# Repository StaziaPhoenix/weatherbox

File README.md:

# Weatherbox
This repository contains code and schematics of the WeatherBox lamp we created for ECE 196 at UC San Diego.
## Contents
* The root directory contains the Arduino code
* The Electrical directory contains Eagle circuit schematics
* The Structural directory contains drawings and Inkscape and SolidWorks schematics

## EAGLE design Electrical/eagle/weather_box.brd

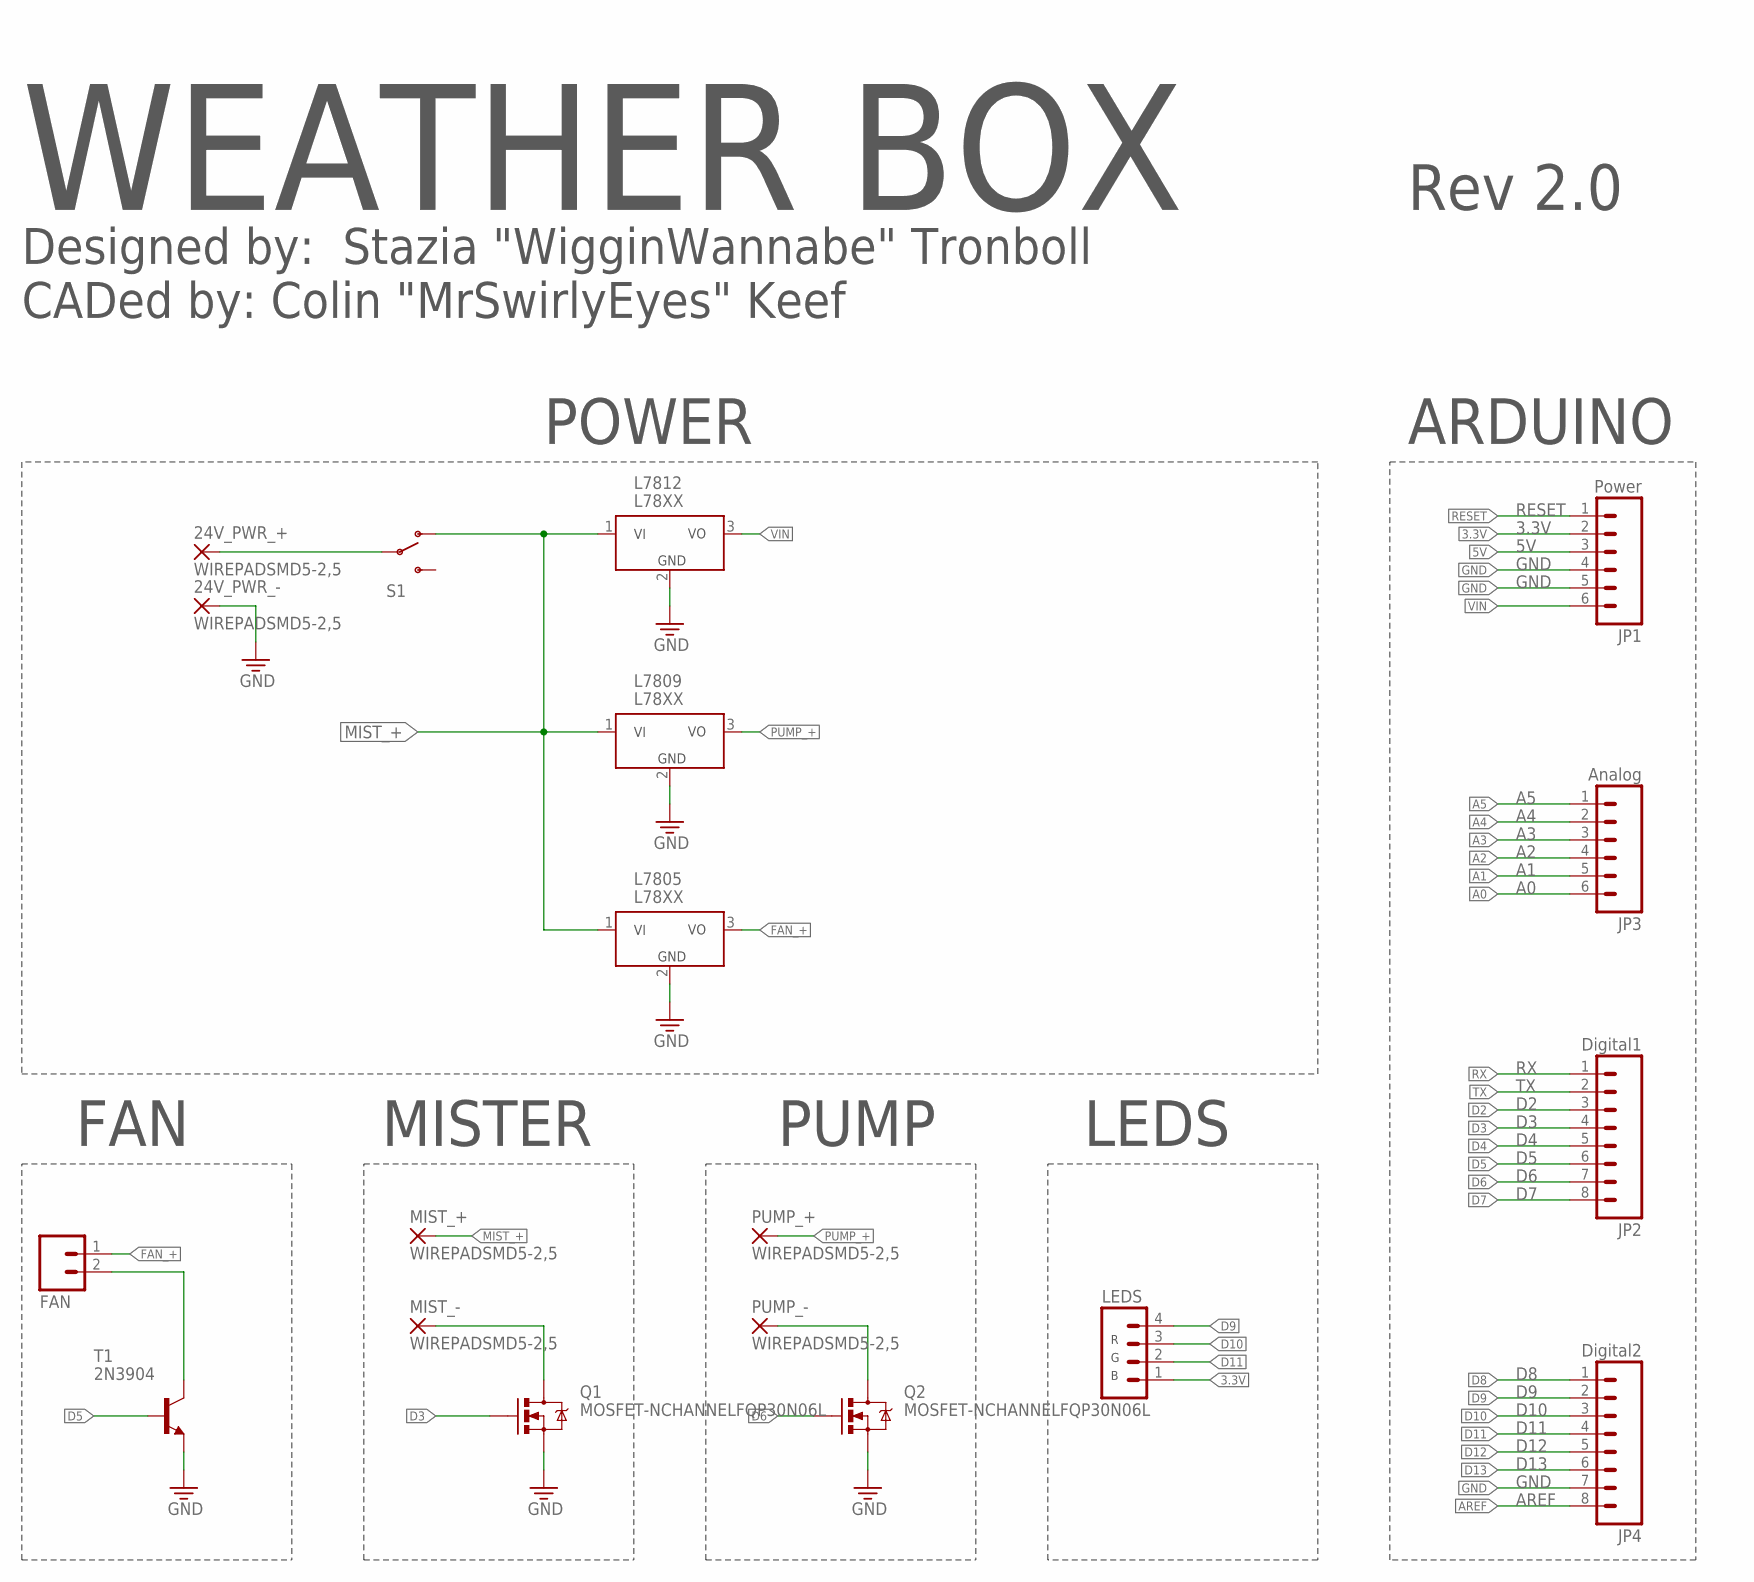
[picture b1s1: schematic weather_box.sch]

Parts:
24V_PWR_+, 24V_PWR_-: WIREPADSMD5-2,5; 5-2,5
FAN: M02PTH; 1X02
JP1: Power; 1X06
JP2: Digital1; 1X08
JP3: Analog; 1X06
JP4: Digital2; 1X08
L7805, L7809, L7812: L78XX; TO-220-HEATSINK
LEDS: M04PTH; 1X04
MIST_+: WIREPADSMD5-2,5; 5-2,5
MIST_-: WIREPADSMD5-2,5; 5-2,5
PUMP_+: WIREPADSMD5-2,5; 5-2,5
PUMP_-: WIREPADSMD5-2,5; 5-2,5
Q1, Q2: MOSFET-NCHANNELFQP30N06L; TO220V
S1: SWITCH-SPDTPTH; SWITCH-SPDT
T1: 2N3904; TO92

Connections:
3.3V: JP1.2, LEDS.1
5V: JP1.3
A0: JP3.6
A1: JP3.5
A2: JP3.4
A3: JP3.3
A4: JP3.2
A5: JP3.1
AREF: JP4.8
D2: JP2.3
D3: JP2.4, Q1.1 (G)
D4: JP2.5
D5: JP2.6, T1.2 (B)
D6: JP2.7, Q2.1 (G)
D7: JP2.8
D8: JP4.1
D9: JP4.2, LEDS.4
D10: JP4.3, LEDS.3
D11: JP4.4, LEDS.2
D12: JP4.5
D13: JP4.6
FAN_+: FAN.1, L7805.3 (VO)
GND: 24V_PWR_-.1, JP1.4, JP1.5, JP4.7, L7805.2 (GND), L7809.2 (GND), L7812.2 (GND), Q1.3 (S), Q2.3 (S), T1.3 (E)
MIST_+: L7805.1 (VI), L7809.1 (VI), L7812.1 (VI), MIST_+.1, S1.1 (O)
unnamed: 24V_PWR_+.1, S1.2
unnamed: MIST_-.1, Q1.2 (D)
unnamed: FAN.2, T1.1 (C)
unnamed: PUMP_-.1, Q2.2 (D)
PUMP_+: L7809.3 (VO), PUMP_+.1
RESET: JP1.1
RX: JP2.1
TX: JP2.2
VIN: JP1.6, L7812.3 (VO)

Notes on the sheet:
FAN
ARDUINO
MISTER
POWER
PUMP
LEDS
WEATHER BOX
Rev 2.0
Designed by: Stazia "WigginWannabe" Tronboll CADed by: Colin "MrSwirlyEyes" Keef

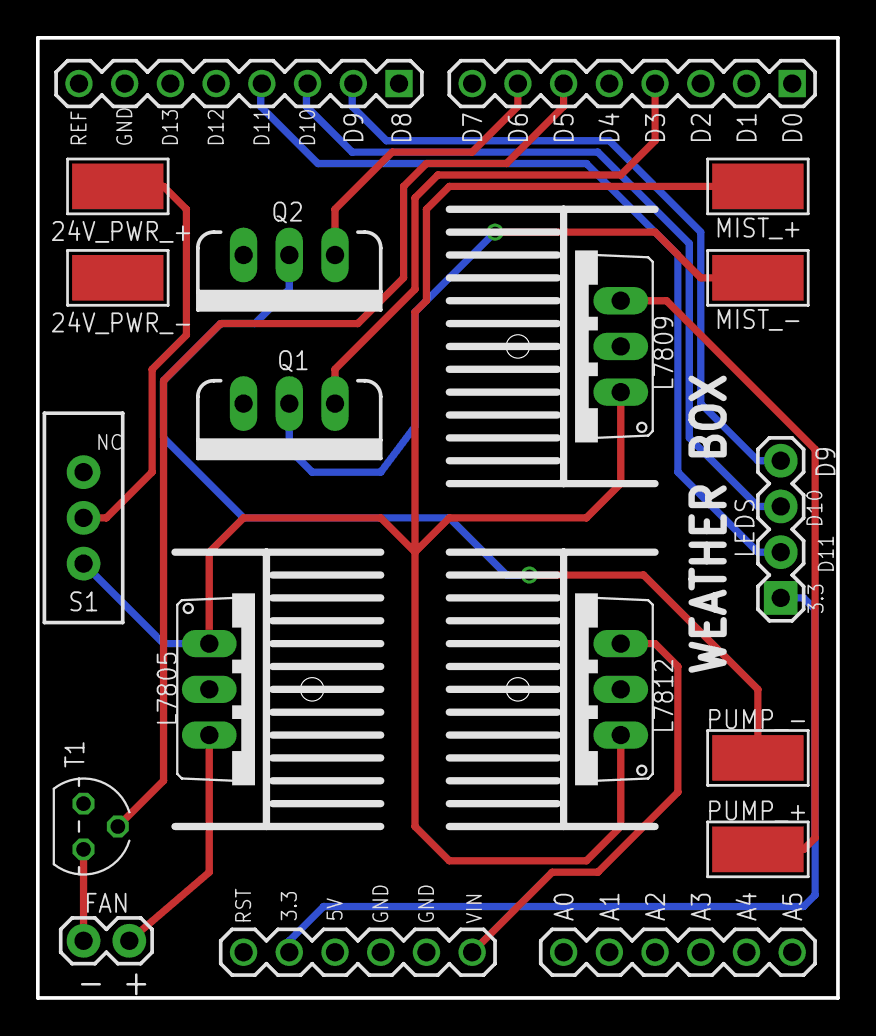
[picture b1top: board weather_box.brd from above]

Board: 2 copper layers, 44.5 x 53.3 mm, 19 parts (0 on the bottom side), 16 nets.

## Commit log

2017-11-21 Include libraries
2017-11-21 Make esp chip a slave, listening for a 1 (request) from the Rx pin and fetch data at request
2017-11-21 remove gpio pin
2017-11-21 next
2017-11-23 wed 11/22 first push
2017-11-23 httpClientStream
2017-11-28 Bring Vladi's code into group repo
2017-11-28 I hate my life
2017-11-30 Connects to AndroidAP, fetches forecast according to hardcoded url
2017-11-30 Nov 29 Working Arduino Code
2018-07-16 Added Electrical and Structural Schematics
2019-07-12 backing up for local computer deletion

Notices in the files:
parts and their libraries:
SparkFun-DiscreteSemi: Licensing: Creative Commons ShareAlike 4.0 International - https://creativecommons.org/licenses/by-sa/4.0
